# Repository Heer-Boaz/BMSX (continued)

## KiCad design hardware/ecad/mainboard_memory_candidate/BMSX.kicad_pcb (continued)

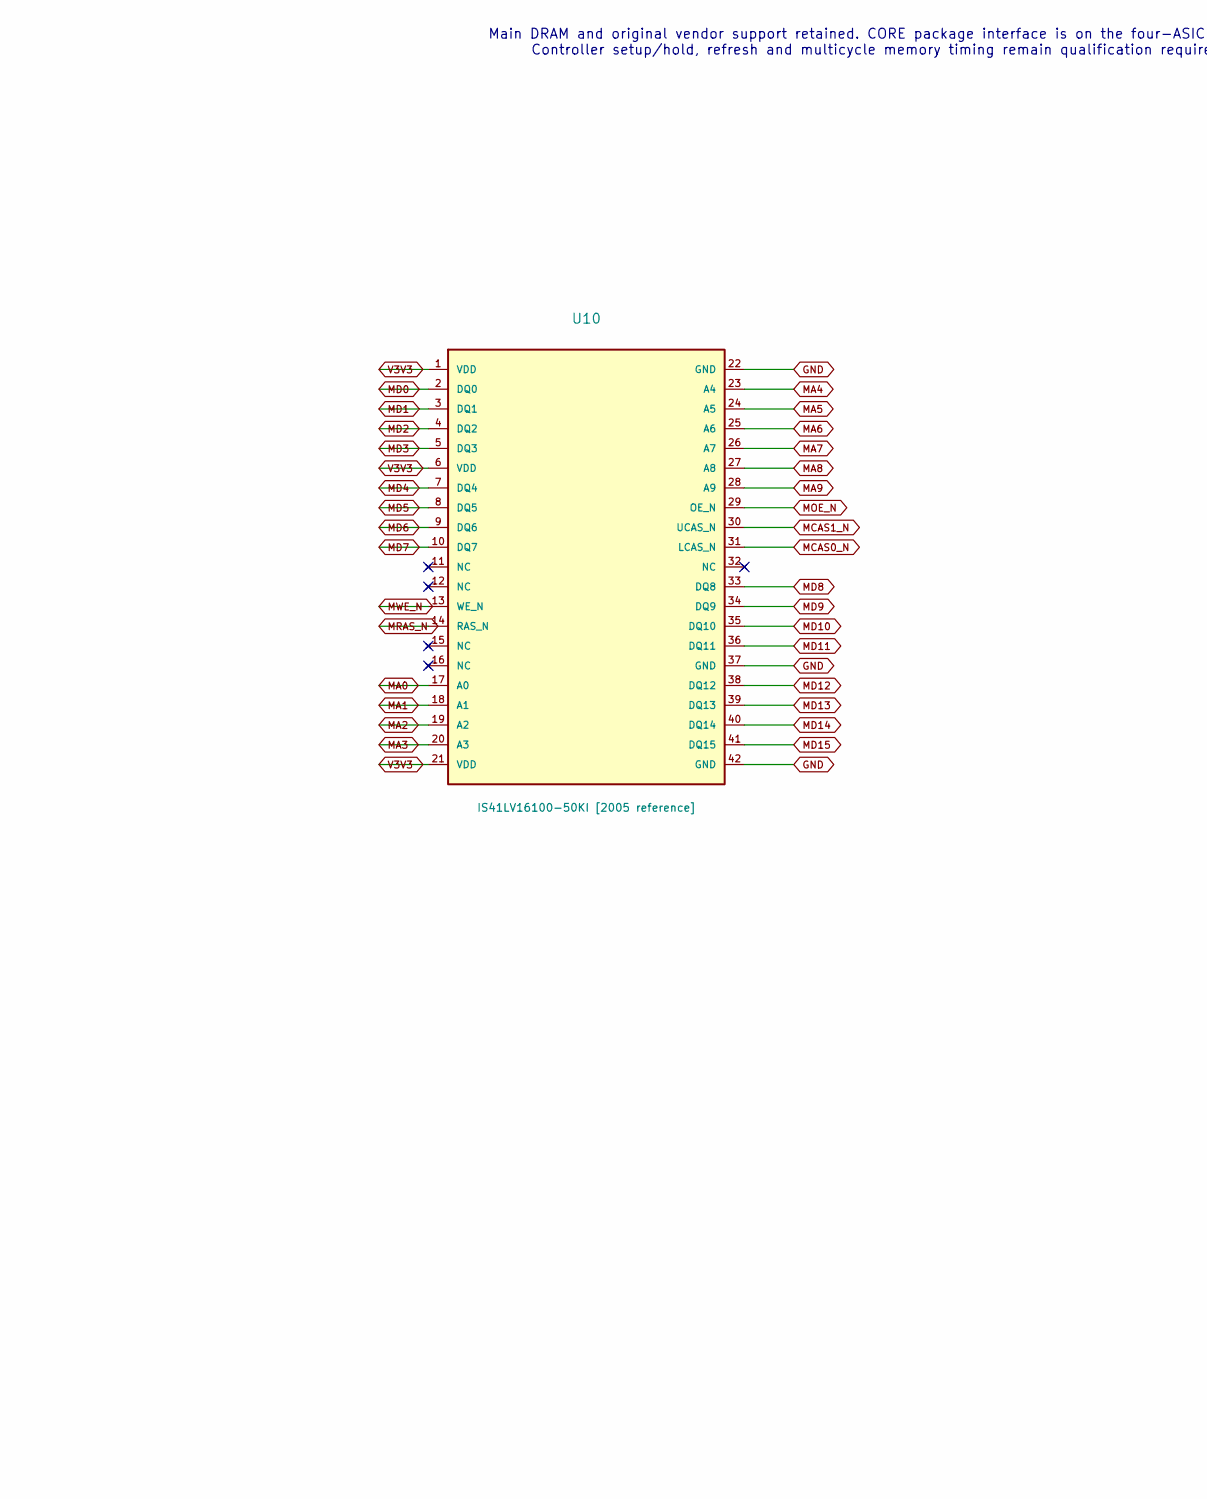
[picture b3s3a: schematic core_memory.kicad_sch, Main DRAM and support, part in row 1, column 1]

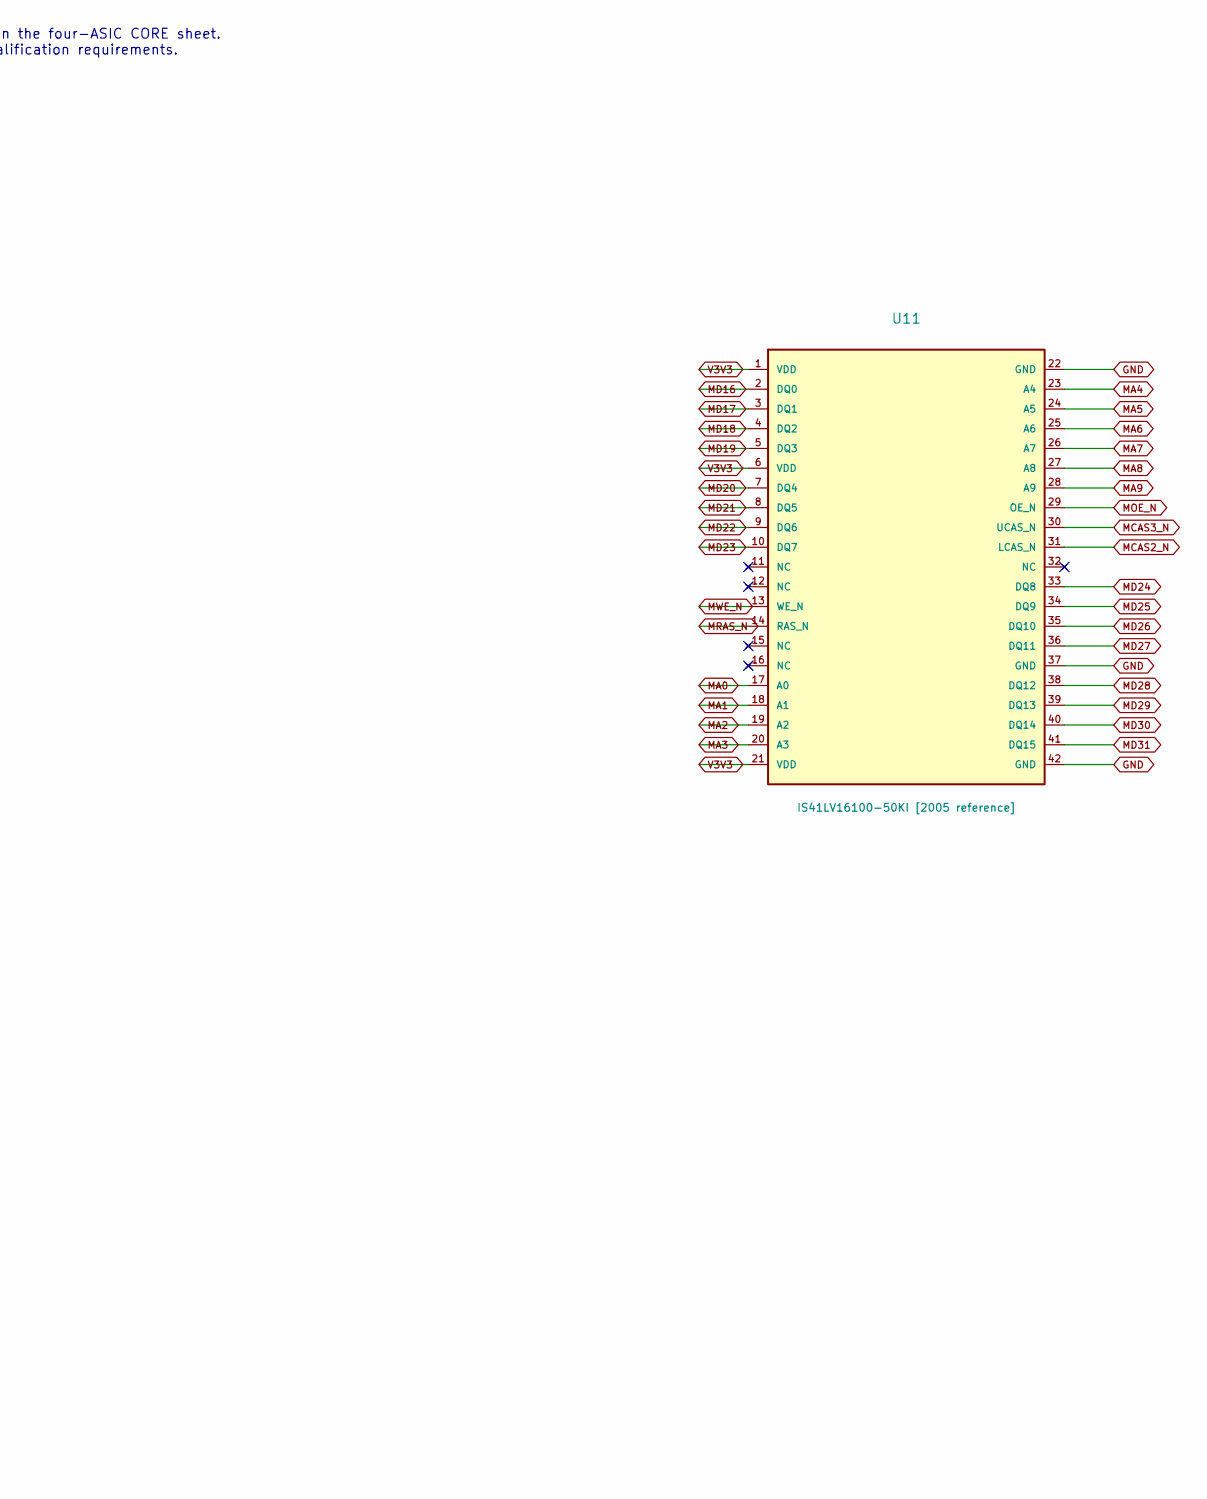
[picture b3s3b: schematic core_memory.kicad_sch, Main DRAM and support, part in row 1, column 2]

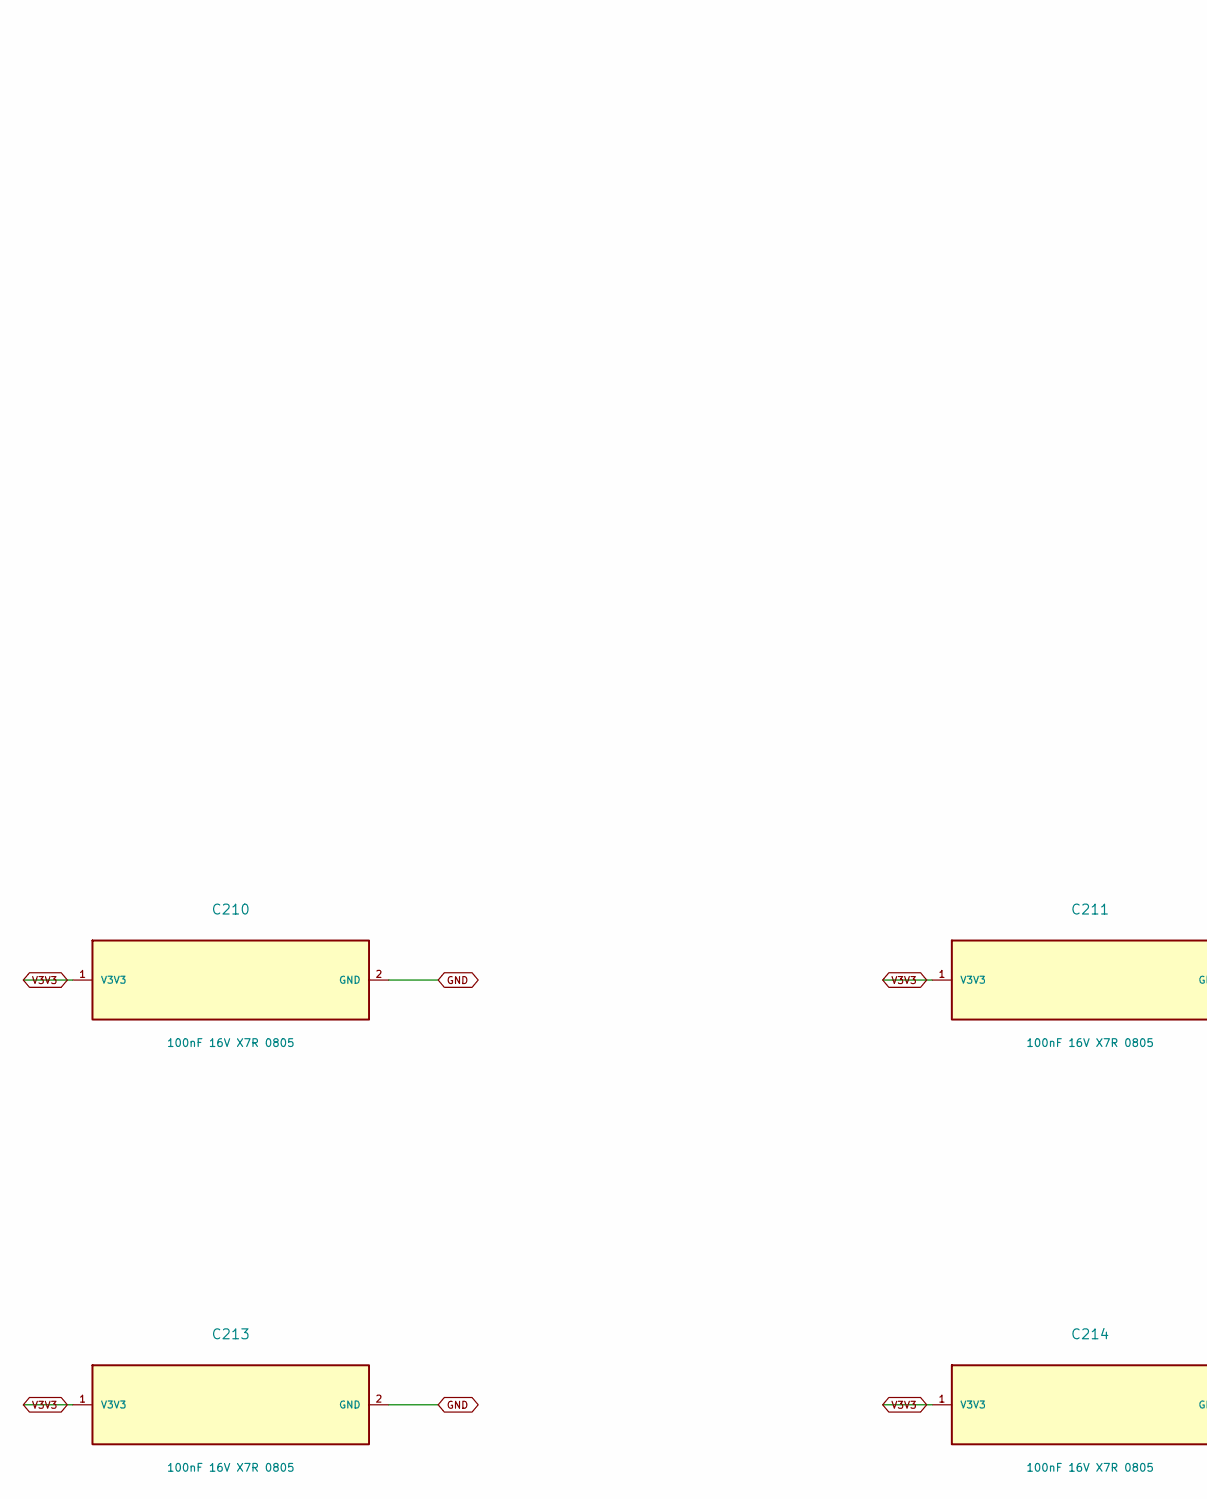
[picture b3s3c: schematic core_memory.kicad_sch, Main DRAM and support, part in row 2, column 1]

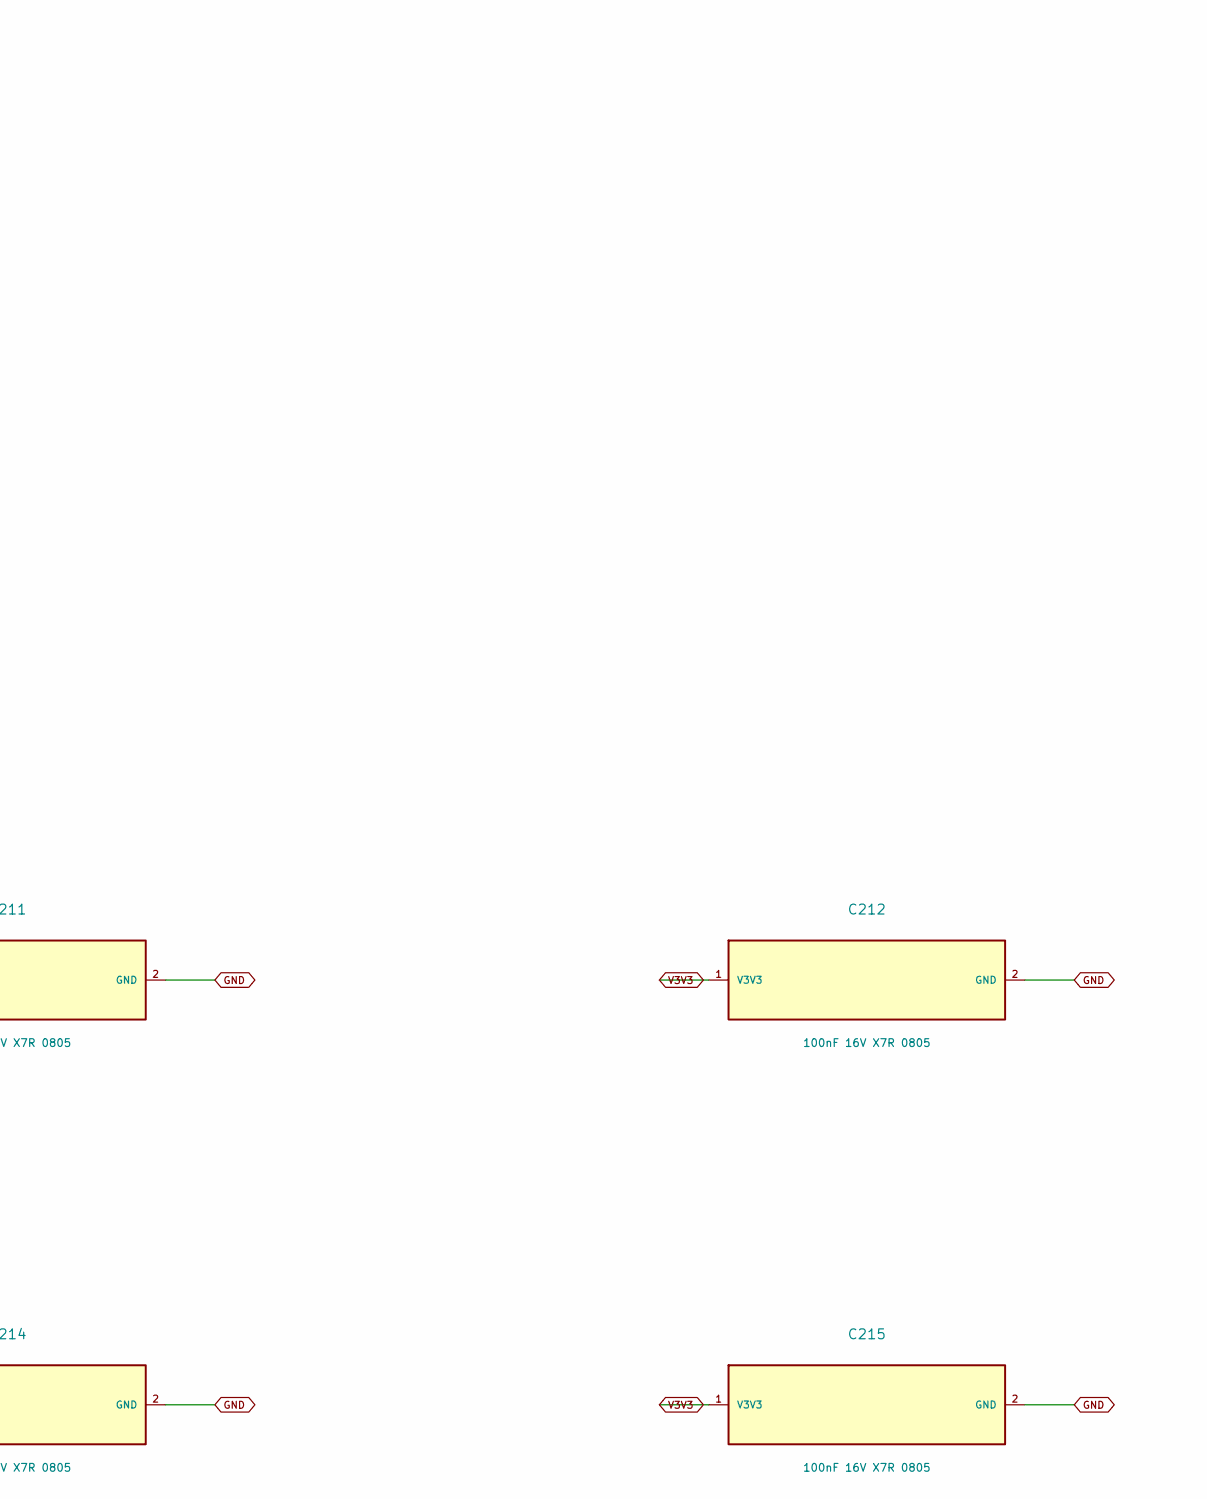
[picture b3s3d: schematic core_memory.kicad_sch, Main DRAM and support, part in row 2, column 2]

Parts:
C210: 100nF 16V X7R 0805; C210
C211: 100nF 16V X7R 0805; C211
C212: 100nF 16V X7R 0805; C212
C213: 100nF 16V X7R 0805; C213
C214: 100nF 16V X7R 0805; C214
C215: 100nF 16V X7R 0805; C215
U10: IS41LV16100-50KI [2005 reference]; U10
U11: IS41LV16100-50KI [2005 reference]; U11

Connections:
GND: C210.2 (GND), C211.2 (GND), C212.2 (GND), C213.2 (GND), C214.2 (GND), C215.2 (GND), U10.22 (GND), U10.37 (GND), U10.42 (GND), U11.22 (GND), U11.37 (GND), U11.42 (GND); also elsewhere on the board
MA0: U10.17 (A0), U11.17 (A0); also elsewhere on the board
MA1: U10.18 (A1), U11.18 (A1); also elsewhere on the board
MA2: U10.19 (A2), U11.19 (A2); also elsewhere on the board
MA3: U10.20 (A3), U11.20 (A3); also elsewhere on the board
MA4: U10.23 (A4), U11.23 (A4); also elsewhere on the board
MA5: U10.24 (A5), U11.24 (A5); also elsewhere on the board
MA6: U10.25 (A6), U11.25 (A6); also elsewhere on the board
MA7: U10.26 (A7), U11.26 (A7); also elsewhere on the board
MA8: U10.27 (A8), U11.27 (A8); also elsewhere on the board
MA9: U10.28 (A9), U11.28 (A9); also elsewhere on the board
MCAS0_N: U10.31 (LCAS_N); also elsewhere on the board
MCAS1_N: U10.30 (UCAS_N); also elsewhere on the board
MCAS2_N: U11.31 (LCAS_N); also elsewhere on the board
MCAS3_N: U11.30 (UCAS_N); also elsewhere on the board
MD0: U10.2 (DQ0); also elsewhere on the board
MD1: U10.3 (DQ1); also elsewhere on the board
MD2: U10.4 (DQ2); also elsewhere on the board
MD3: U10.5 (DQ3); also elsewhere on the board
MD4: U10.7 (DQ4); also elsewhere on the board
MD5: U10.8 (DQ5); also elsewhere on the board
MD6: U10.9 (DQ6); also elsewhere on the board
MD7: U10.10 (DQ7); also elsewhere on the board
MD8: U10.33 (DQ8); also elsewhere on the board
MD9: U10.34 (DQ9); also elsewhere on the board
MD10: U10.35 (DQ10); also elsewhere on the board
MD11: U10.36 (DQ11); also elsewhere on the board
MD12: U10.38 (DQ12); also elsewhere on the board
MD13: U10.39 (DQ13); also elsewhere on the board
MD14: U10.40 (DQ14); also elsewhere on the board
MD15: U10.41 (DQ15); also elsewhere on the board
MD16: U11.2 (DQ0); also elsewhere on the board
MD17: U11.3 (DQ1); also elsewhere on the board
MD18: U11.4 (DQ2); also elsewhere on the board
MD19: U11.5 (DQ3); also elsewhere on the board
MD20: U11.7 (DQ4); also elsewhere on the board
MD21: U11.8 (DQ5); also elsewhere on the board
MD22: U11.9 (DQ6); also elsewhere on the board
MD23: U11.10 (DQ7); also elsewhere on the board
MD24: U11.33 (DQ8); also elsewhere on the board
MD25: U11.34 (DQ9); also elsewhere on the board
MD26: U11.35 (DQ10); also elsewhere on the board
MD27: U11.36 (DQ11); also elsewhere on the board
MD28: U11.38 (DQ12); also elsewhere on the board
MD29: U11.39 (DQ13); also elsewhere on the board
MD30: U11.40 (DQ14); also elsewhere on the board
MD31: U11.41 (DQ15); also elsewhere on the board
MOE_N: U10.29 (OE_N), U11.29 (OE_N); also elsewhere on the board
MRAS_N: U10.14 (RAS_N), U11.14 (RAS_N); also elsewhere on the board
MWE_N: U10.13 (WE_N), U11.13 (WE_N); also elsewhere on the board
V3V3: C210.1 (V3V3), C211.1 (V3V3), C212.1 (V3V3), C213.1 (V3V3), C214.1 (V3V3), C215.1 (V3V3), U10.1 (VDD), U10.6 (VDD), U10.21 (VDD), U11.1 (VDD), U11.6 (VDD), U11.21 (VDD); also elsewhere on the board

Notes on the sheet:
Main DRAM and original vendor support retained. CORE package interface is on the four-ASIC CORE sheet. Controller setup/hold, refresh and multicycle memory timing remain qualification requirements.

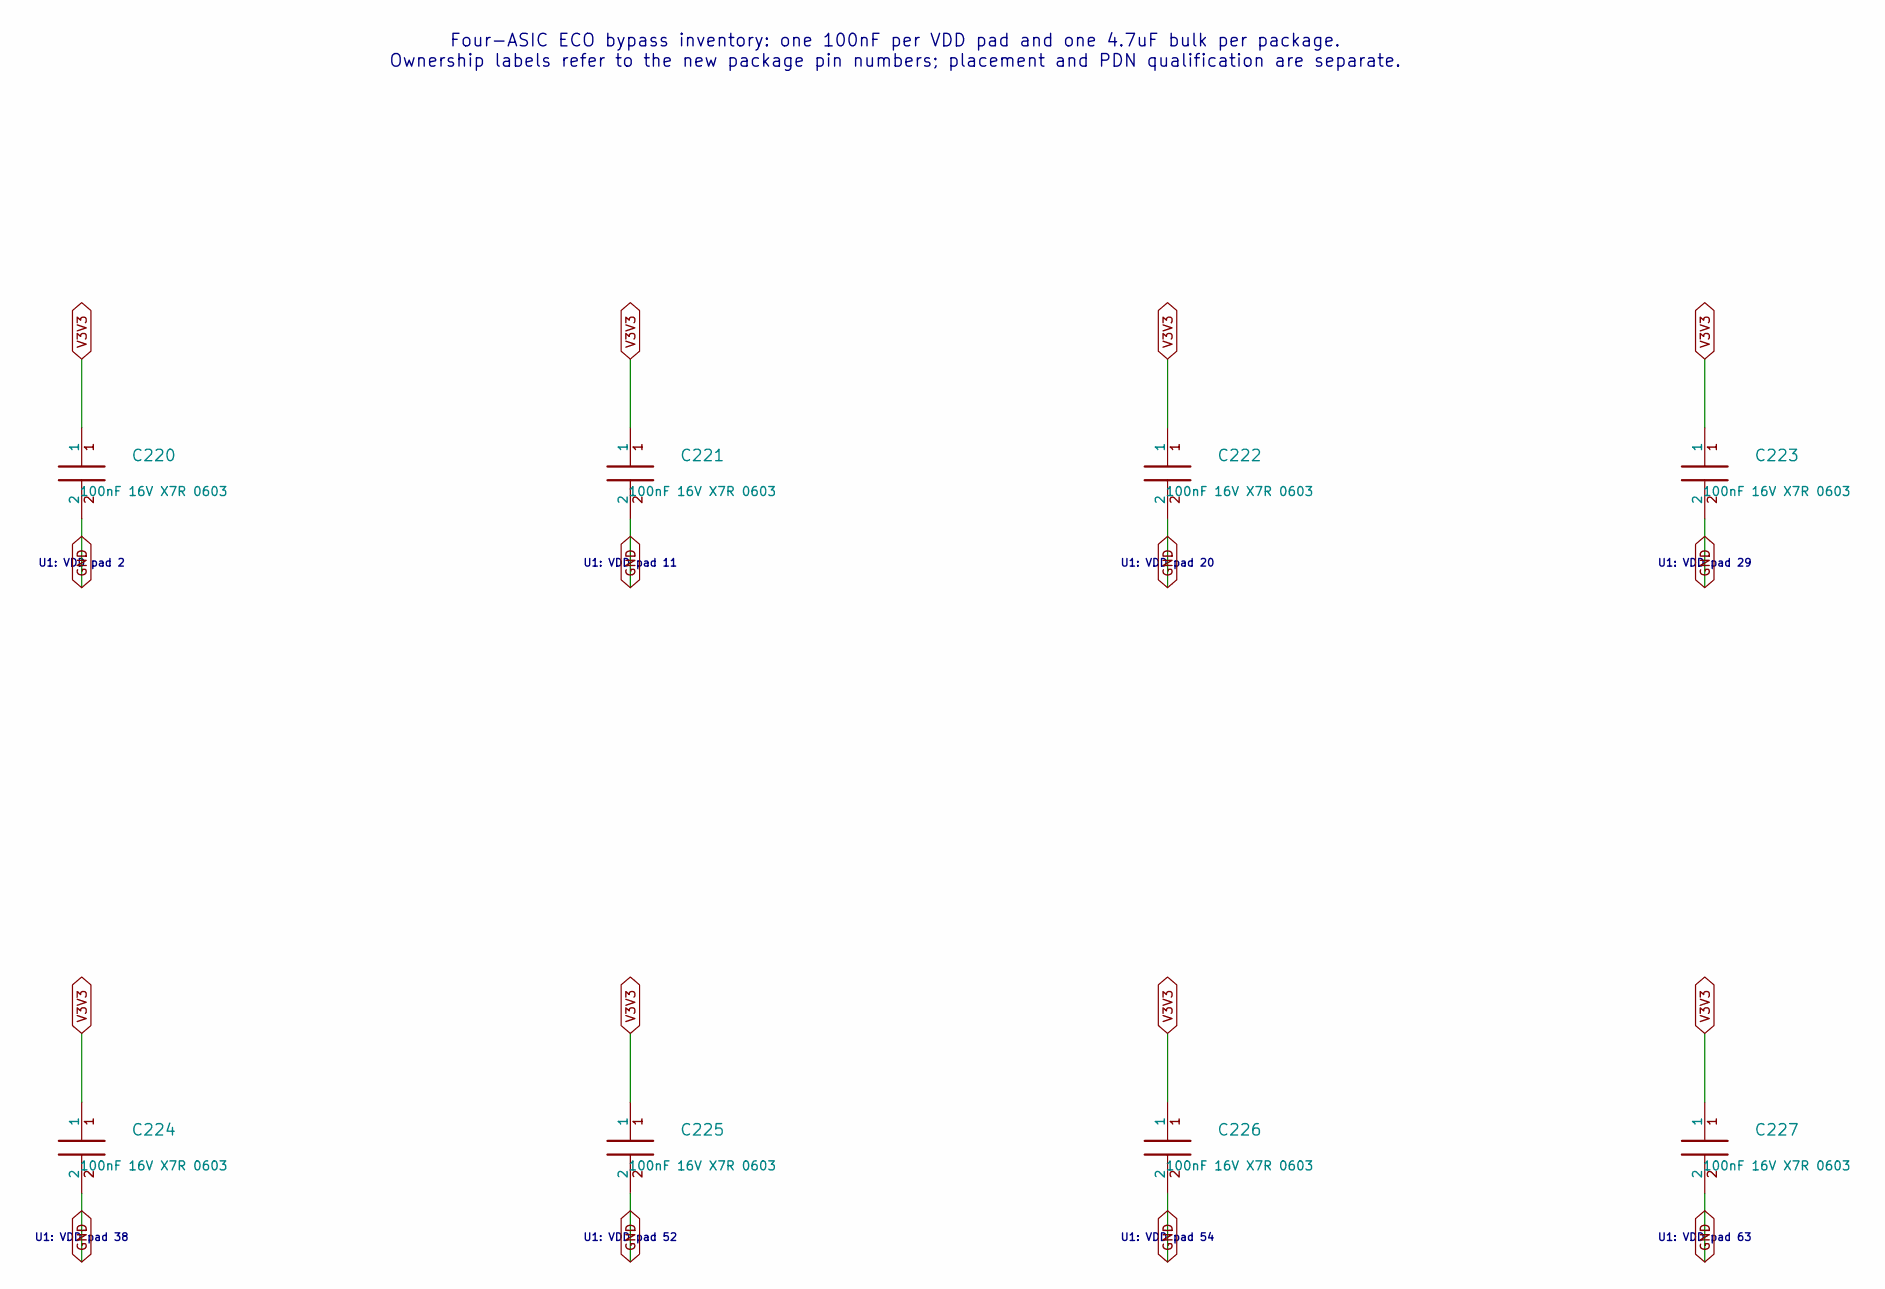
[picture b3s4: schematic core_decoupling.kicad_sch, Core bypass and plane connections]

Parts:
C220: 100nF 16V X7R 0603; C220
C221: 100nF 16V X7R 0603; C221
C222: 100nF 16V X7R 0603; C222
C223: 100nF 16V X7R 0603; C223
C224: 100nF 16V X7R 0603; C224
C225: 100nF 16V X7R 0603; C225
C226: 100nF 16V X7R 0603; C226
C227: 100nF 16V X7R 0603; C227

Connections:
GND: C220.2, C221.2, C222.2, C223.2, C224.2, C225.2, C226.2, C227.2; also elsewhere on the board
V3V3: C220.1, C221.1, C222.1, C223.1, C224.1, C225.1, C226.1, C227.1; also elsewhere on the board

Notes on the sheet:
Four-ASIC ECO bypass inventory: one 100nF per VDD pad and one 4.7uF bulk per package. Ownership labels refer to the new package pin numbers; placement and PDN qualification are separate.
U1: VDD pad 2
U1: VDD pad 11
U1: VDD pad 20
U1: VDD pad 29
U1: VDD pad 38
U1: VDD pad 52
U1: VDD pad 54
U1: VDD pad 63
